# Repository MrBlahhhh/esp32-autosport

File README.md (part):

# ESP32-S3 CAN + microSD Automotive Logger — Rev B

## TL;DR

A data logger you wire straight into a race car: 12 V and CAN come in on one
4-pin plug, sensor readings and CAN traffic get written to a microSD card.

- **You cannot kill it with the wiring.** Battery backwards? Blocks it,
  forever, no blown fuse. Alternator load dump, jump start, ignition spikes?
  Clamped. A sensor wire shorted to 12 V? That channel's fuse trips, the
  board keeps logging.
- **Ignition-off doesn't corrupt the card.** The board sees the power cut
  ~150 ms before it actually dies and uses that time (banked in two big
  capacitors) to finish the write and close the file.
- **4 sensor inputs, jumper-set for 0–3.3 V / 0–5 V / 0–16 V**, readable
  fast-and-rough on the ESP32's own ADC or slow-and-precise on a 16-bit
  ADS1115. Plus battery voltage monitoring, USB-C, a WS2812 shift-light
  header, and spare I/O.
- **The Python in `gen/` is the real source.** It generates, places, routes,
  audits, and circuit-simulates the whole board; the KiCad files are build
  outputs. `python gen/build_board.py` rebuilds the PCB from nothing, and
  [`gen/README.md`](gen/README.md) documents the whole pipeline — including
  the schematic-drawing conventions — so the next board can reuse it.
- **The firmware runs before the board exists.** `gen/simulate_firmware.py`
  compiles the sketch for the PC against a model of this board and feeds it
  CAN frames, sensor voltages and an ignition cut. Porting the proven MINI R53
  shift-light firmware to this hardware turned up five defects that no ERC,
  DRC or SPICE run can see — including a wideband that reads 17 % high and a
  sensor rail that never powers up.
- **State: routed clean, simulated, firmware ported, never manufactured.**
  Order a small prototype run first.

---

A single-CAN, single-microSD ESP32-S3 board with a motorsport-grade front end:
reverse-battery protection that survives being hooked up backwards indefinitely,
load-dump clamping, and four analog sensor inputs whose dividers are selected by
solder jumpers.

Feature set is deliberately close to the Autosport Labs ESP32-CAN-X2 and the
ESP32 Dual CAN-FD dev board — same ESP32-S3-WROOM-1 module, same 4-pin JST-PH
harness convention (12 V / GND / CAN_H / CAN_L), same jumper-selectable 120 Ω
termination — but trades the second CAN channel for an onboard microSD socket
and conditioned analog inputs. Termination ships **off** here rather than on,
which is the one place this board deliberately breaks with that convention:
the common case is plugging into a vehicle bus that is already terminated.

**Status: Rev B, fully routed.** Schematic is ERC-clean on KiCad 9.0. The PCB
is **84 x 100 mm**, 4-layer, **fully placed and routed with zero DRC errors and
nothing unconnected** — 1731 tracks, 323 vias, 206 footprints, 115 nets. Rev B
carries the fixes from an external datasheet review (§7): the LM74700 enable
divider, the ANODE capacitor, two TVS standoff corrections, transient clamps
on the analog harness inputs, and a dozen smaller items. `fab/` holds the
Gerbers, drill, BOM and pick-and-place in JLCPCB's format, BOM and CPL verified
to list the same 167 designators. See §9 for how the board is built, §10 for
what simulation and the physical audit say about it, and §11 for
the ordering steps. **Nothing has ever been fabricated — the first order should
be a small prototype run.**

---

## 1. Specification

| | |
|---|---|
| MCU | ESP32-S3-WROOM-1-N16R8 (16 MB flash, 8 MB octal PSRAM) |
| Supply input | 6–36 V continuous, reverse-protected to −65 V, transients clamped at 64.5 V, 154 ms power-cut ride-through (51 ms worst-case on a flat battery) |
| CAN | 1× CAN 2.0B, TJA1051T/3, ESP32-S3 TWAI controller, split termination, **off by default** |
| Storage | microSD, 4-bit SDMMC, switchable card supply |
| Analog in | 4 channels, solder-jumper divider, **0–5 V by default** (0–3.3 V / 0–16 V by jumper) + optional pull-up bias, shared by the ESP32 ADC and a 16-bit ADS1115 |
| Extras | Battery voltage monitor, USB-C (native USB), I²C/Qwiic, UART0, SPI breakout, WS2812 5 V DIN header, 6-pin spare-IO header |
| Rails | +5 V @ 1 A, +3V3 @ 1 A, +5 V sensor excitation (separately fused) |
| Parts | 195 component instances, 97 distinct BOM lines, all surface-mount except 8 through-hole connectors |

---

## 2. Power chain

```
J1.1 ──[F1 2A]──┬──[FB1 ferrite]── LM74700-Q1 + Q1 (ideal diode) ──┬── +VBAT
                │                                                  ├── C3 100µF bulk
                └── D1 SMCJ40CA clamp                              ├── U3 LM5164 ─→ +5V ─[PF1]─→ +5VS
                    (ahead of the FET)                             └── U4 LM5164 ─→ +3V3
```

### Reverse-battery protection

`U1` (LM74700-Q1) drives `Q1`, a 100 V N-channel MOSFET, as an ideal diode.
`Q1`'s **source faces the battery and its drain faces the load**, so the body
diode points forward: current passes in normal operation, and with the battery
connected backwards the body diode is reverse-biased and the FET is held off.
Nothing conducts, nothing gets hot, and the fuse does not blow — you can hook it
up backwards all day.

The forward drop is the FET's I·R (6.8 mΩ × 0.5 A ≈ 3 mV) rather than a diode's
0.4 V, so nothing is wasted in normal running either.

**Order matters here.** `D1`, the transient clamp, sits *ahead* of the blocking
FET. Clamping downstream of it leaves `Q1` and the LM74700 exposed to whatever
arrives on the harness: on a negative transient `Q1` turns off and stands the
whole pulse across its drain-source, and pulses 1 (−100 V) and 3a (−150 V) both
exceed its 100 V rating. In front of the FET the clamp catches those first —
simulation puts `Q1` at 55 V during pulse 1, against 100 V (§10).

That placement is only safe because `D1` is **bidirectional**. A unidirectional
part in this position would forward-conduct on a sustained reverse connection
and blow `F1`, which is exactly the outcome the ideal diode exists to avoid. At
40 V standoff either way, a −14 V reverse battery is still `Q1`'s job to block
and only real transients are clamped.

`R1`/`R2` set the LM74700 UVLO so the board enables at roughly 5.9 V and drops
out cleanly during cranking rather than browning out in an undefined state.

### Transient rating and its assumption

`D1` is an SMCJ40CA: 40 V standoff either polarity, 64.5 V clamping at 1500 W
(10/1000 µs). 40 V rather than 33 V so the part stands off the declared 36 V
top of the input window instead of sitting in conduction there.

That covers **ISO 7637-2 pulse 5b with centralised load-dump suppression**
(test level ~35 V), which is what any alternator with an internal avalanche
clamp produces — i.e. everything built in the last several decades. Simulation
(§10) shows the harness reaching 31 V in that case with the TVS never
conducting at all. Pulses 1, 2a, 3a and 3b are likewise covered: the worst is
pulse 1, where the clamp takes 0.07 J against roughly 2 J of capability at that
pulse width. A 24 V jump-start sits below the standoff voltage so it does not
conduct.

It does **not** cover unsuppressed load dump. At the pulse 5b level IV of 87 V
the clamp is asked to absorb 219 J against about 6.7 J of capability and is
destroyed (§10). That needs a higher-energy clamp or a series pre-regulator —
**say so if the target vehicle has an external-regulator alternator.**

Both bucks are LM5164s rated to **100 V**, so at the 64.5 V clamp level there
is still headroom on the switcher inputs; the clamp fires before anything
downstream is stressed. The tighter limit is the LM74700's own 65 V, which the
clamp level sits directly on top of — another reason the unsuppressed case is
out of scope rather than marginal.

### Why two bucks instead of a buck plus an LDO

`U3` (+5 V) and `U4` (+3V3) both run directly off `+VBAT`. It costs one extra
inductor versus 12 V→5 V→3.3 V cascading, and buys two things:

1. **Fault isolation.** A shorted 5 V sensor wire in the harness loads `U3`
   and trips `PF1`, but `U4` and the MCU never see it. A cascaded 3.3 V rail
   would collapse with the 5 V rail.
2. **No heat.** A 5 V→3.3 V linear at 600 mA burns ~1 W, which in an engine
   bay at 85 °C ambient is a thermal problem in a small package. A switcher
   burns almost nothing.

Both parts are the same LM5164, so it is one line on the BOM in quantity 20
rather than two different regulators.

### Power-fail detection and ride-through

The ignition cuts this board's power with a log file open on the SD card,
every single drive. The chain that makes that survivable:

1. **Detect** — a TLV431 watches `VBAT_F` *ahead* of Q1 through a 100k/12.7k
   divider and asserts `PWR_FAIL` (GPIO15, rising edge) when the harness
   drops below **11.0 V**. Sensing ahead of the ideal diode is the point:
   when the ignition opens, the harness collapses within microseconds while
   `+VBAT` coasts, so the warning arrives before any stored energy has been
   spent. A 1 M feedback resistor adds ~0.3 V of hysteresis so cranking sag
   cannot chatter the interrupt.
2. **Coast** — `+VBAT` holds 760 µF (100 µF + 2 × 330 µF/100 V). Energy is
   ½CV², so the bank lives on the input rail where a volt is worth most.
3. **Shed** — `SENS_EN` (GPIO16) drives a 2N7002 + AO3401 high-side switch on
   the sensor rail. Sensors are external loads firmware cannot otherwise
   turn off, and at four × 20 mA they double the drain. The switch is off at
   reset — the rail comes up only when firmware asks.

Simulated end to end (§10, `sim/ridethru.png`): detection in under 1 ms, and
from `PWR_FAIL` to the converters dropping out is **154 ms with the sensor
rail shed, 75 ms without** — both measured on the 760 µF bank.

That is the *healthy-battery* case: the ignition opens at 13.5 V and `+VBAT`
starts its coast from there, because `Q1` isolates it from the harness. Open
the ignition on a battery already down at the trip point and the bank starts
at 10.7 V instead — energy goes as V², so that alone is 1.9× less charge. The
Monte Carlo puts that flat-battery corner at **78 ms median, 51 ms at 0.1 %**
with worst-case tolerances (§10). Both are real; they bound opposite ends of
the same event, and firmware should be sized against the 51 ms.

**Firmware contract:** on `PWR_FAIL` rising — drop `SENS_EN`, stop sampling,
flush and close the file, then idle. Do not start a new write while
`PWR_FAIL` is high. The window is guaranteed by hardware; spending it is
firmware's job.

The firmware that spends it now exists and has been run against that window
(§10, *Firmware in the loop*). Measured: the file is closed **31 ms** after
`PWR_FAIL`, leaving 121 ms of the bank unspent, and the card may take up to a
**~130 ms** flush before the close no longer fits — though that, too, is
against the nominal window; on the flat-battery corner the budget is 51 ms and
only a healthy card fits. That is roughly seven times a
healthy card's latency but it is a limit, not unlimited protection — a card
that stalls for longer than that still loses the file.

### Reversed 5 V on the exposed 5 V pins

Asked and answered per connector: **USB-C** cannot be reversed through the
connector (VBUS/GND positions are fixed; the plug is rotation-symmetric).
**J10 sensor +5VS** survives a reversed 5 V by design — D3 forward-conducts
at −0.7 V and PF1 trips, resettable. A **backwards WS2812 strip** trips PF3;
the strip is on its own. **J8 rail break-out is unprotected** — it is a bare
bench header, and a reversed supply clipped onto it lands directly on the
+5 V rail's loads. Treat J8 like any bare rail.

### 5 V sensor excitation

`+5VS` is the +5 V rail behind the `SENS_EN` load switch, `PF1` (200 mA hold
/ 400 mA trip polyfuse), a ferrite, and `D3` (SMAJ6.0A). A sensor wire
shorted to chassis or to battery trips the polyfuse and clamps the transient
without taking the board down — and a tripped rail can now also be cycled
from firmware instead of waiting for the polyfuse to cool.

Note this is a *fused tap off the 5 V rail*, not a separately regulated
reference. For ratiometric sensors where absolute accuracy matters, the ADC
should ratio against a measurement of `+5VS` — or add a dedicated precision
reference. See §7.

---

## 3. Analog input conditioning

Each of the four channels is identical:

```
AINn_IN ──[1k series]──┬─────────[10k]────┬── AINn ──→ ADC
                       │                  │
                  [JPn PULLUP]        [JPn BYPASS] (shorts the 10k)
                       │                  │
                    2.49k             [JPn RANGE] ─┬─[15k]─ GND   (position A)
                       │                           └─[2.21k]─ GND (position B)
                    +5VS                  │
                                    [100nF] + BAT54S clamp to GND / +3V3
```

### Jumper matrix

| RANGE | BYPASS | Input range | Ratio | At the ADC | Clips at | Typical sensor |
|---|---|---|---|---|---|---|
| **A** | open | **0–5.0 V — ships like this** | 0.5769 | 2.885 V at 5.0 V in | 5.37 V in | MAP, TPS, wideband AFR, most 5 V sensors |
| open | **closed** | 0–3.3 V | 1.0000 | 3.300 V at 3.3 V in | 3.10 V in | 3.3 V-native sensor, ratiometric output |
| **B** | open | 0–16 V | 0.1673 | 2.677 V at 16.0 V in | 18.53 V in | Battery-referenced signals, 12 V switch inputs |

**All four channels ship in the 0–5 V position** — `RANGE` bridged 1–2,
`BYPASS` open — because that is what almost every automotive sensor is, and
because it means the firmware's `DIVIDER_GAIN` matches the board as delivered
rather than assuming a jumper somebody has to remember to fit. Cut the 1–2
bridge to move a channel to either of the other two rows.

The upper leg is the 1 k series resistor plus the 10 k, so 11 k against 15 k
gives 15/26 = 0.5769 on the 5 V range and 2.21/13.21 = 0.1673 on the 16 V one.

**These deliberately do not divide to 3.3 V.** The ESP32-S3 ADC tops out near
3.10 V at 12 dB attenuation, and a divider scaled to land exactly there has no
margin: a 5 V sensor rail is rarely exactly 5.000 V, and anything that
overshoots clips silently at full scale — which reads as a plausible-but-wrong
value rather than an obvious fault. At 0.5769 a 5 V channel does not clip until
5.37 V in. The 1:1 mode is the exception and has no headroom by design; it
assumes a sensor that genuinely cannot exceed 3.3 V. The BAT54S clamps protect
the pin either way, but clamping is protection, not measurement.

Source impedance at the ADC node is 11 k ∥ 15 k = **6.35 kΩ** on the 5 V range
(1.84 kΩ on the 16 V range). With the 100 nF filter cap that puts the −3 dB
point at about 250 Hz — ideal for AFR, temperature and pressure, and the limit
if you ever want something fast on a channel.

`PULLUP` is independent of the above: closing it puts 2.49 kΩ to `+5VS` on the
input node, turning the channel into a bias network for **2-wire NTC sensors**
(coolant, oil, air temp) or open-collector/switch-to-ground inputs. Leave it
open for anything that drives its own output.

Every channel lands on **ADC1** (`GPIO1`, `GPIO2`, `GPIO4`, `GPIO5`), which is
the half of the ESP32-S3 ADC that keeps working while WiFi is active. ADC2 is
unusable with WiFi up — that constraint drove the pin assignment.

The same four conditioned nodes also feed `U13`, an **ADS1115** (16-bit
delta-sigma, on the existing I²C bus at 0x48). The ESP32-S3's internal ADC is
only good for ±1–2 % even after calibration — ±0.2 AFR on a 0–5 V wideband
output — so firmware picks per channel: fast-and-rough on the internal ADC, or
slow-and-accurate (up to 860 SPS) on the ADS1115. The divider resistors are
0.1 % thin-film so the front end does not throw away what the converter buys,
and the note in the schematic records that the 1 k series resistor is part of
the divider chain — the exact scale factor is a firmware calibration constant.

`R77` (100 k) and `R64` (10 k) divide `+VBAT` by 11 onto `GPIO6` for
battery-voltage logging: 14.0 V reads 1.27 V, and the 36 V top of the input
range reads 3.27 V.

---

## 4. CAN

`U12` is a TJA1051T/3 — 5 V bus drive with a separate `VIO` pin tied to +3V3, so
the ESP32 sees 3.3 V logic with no level shifter. `S` is pulled low by `R54`
(10 k) so the transceiver comes up in normal mode with the MCU still in reset;
`GPIO21` can raise it for silent (listen-only) sniffing. `CAN_TX` has no
external pull — the TJA1051 pulls TXD high internally, so a floating pin at
boot is recessive and a bare board cannot jam the bus.

Bus side, in order from the transceiver out:

- `L3` common-mode choke — TDK ACT45B-510-2P-TL003, 51 µH, AEC-Q200. The
  footprint is project-local (`footprints/esp32autosport.pretty`) and its pads
  are renumbered so the symbol's winding 1–2 maps to the package.
- Split termination: `R55`/`R56`, two 60.4 Ω in series with `C28` 4.7 nF to
  ground at the midpoint. Split termination beats a single 120 Ω resistor
  because it gives the common-mode noise somewhere to go instead of
  reflecting it.
- `JP1` in series with the top half — **open by default: the board ships
  unterminated**. Bridge the pads only when this board is an end node on a bus
  of its own. Every vehicle bus, OBD-II diagnostics included, is already
  terminated at both ends, and a third 120 Ω across the pair takes it to about
  40 Ω and can stop it working. This deliberately departs from the Autosport
  Labs convention of shipping terminated, because the common case here is
  plugging into a car that is already correct.
- `D6`/`D7` SMAJ26CA bidirectional clamps to ground on each line.

CAN_H/CAN_L run to `J1` pins 3 and 4, so one 4-pin JST-PH carries power and bus
in a single harness.

### OBD-II and "K-DCAN"

A BMW/MINI K+DCAN cable carries **two unrelated buses**, and this board has
hardware for exactly one of them.

**D-CAN — yes, already.** Diagnostic CAN is ISO 15765-4: plain 500 kbit/s CAN
on OBD-II pins 6 and 14, which is what `U12` and the TWAI controller do. `J1`
maps onto an OBD-II plug with nothing in between — pin 16 to `J1.1`, pins 4/5
to `J1.2`, pin 6 to `J1.3`, pin 14 to `J1.4` — so one cable both powers the
board and connects it to the bus. What is left is software: ISO-TP
(ISO 15765-2) segmentation and whichever of UDS or KWP2000 the target speaks.

> **Termination is already off.** `JP1` ships open (§4), which is what a
> vehicle bus wants — it is already terminated at both ends, and a third
> 120 Ω across the pair drops it to ~40 Ω and can stop it working entirely.
> So there is nothing to cut before plugging into a car; bridge `JP1` only
> for a bench bus where this board is an end node. Note also
> that `CAN_S` (GPIO21) lets firmware pick listen-only for sniffing, so the
> board need never ACK a bus it is only observing.

**K-line — no, and it cannot be bodged.** ISO 9141-2 / KWP2000 is a single
bidirectional wire on OBD-II pin 7 idling at battery voltage and pulled to
ground by an open-collector driver. That needs a transceiver — an L9637D or
equivalent — and there is none on this board. Feeding it into an analog input
does not work either: on the 0–16 V setting the anti-alias filter rolls off at
891 Hz (§10), which destroys even 9600 baud, and it gives no way to transmit.
Routing it to `J7` is worse, since those are strapping pins and a K-line
idling high at boot would hold `IO46` in the wrong boot mode.

This matters for the **MINI R53** specifically: its instrument CAN carries
`0x316` at 500 kbit/s, which this board already reads and logs — but its
*diagnostics and flashing* are K-line at 9600 8E1, negotiating to 62500 baud
for flash reads. The shift light and telemetry work on this hardware. A
tuning or flashing tool does not.

Adding it needs an external L9637D module on the `J5` SPI header — the S3's
UARTs matrix onto any GPIO, so two of `GPIO40`–`42`/`47` become K-line TX/RX,
and `J5` supplies +3V3 and ground. The one wire `J5` cannot supply is the
transceiver's battery feed: `J8` breaks out +5 V, +3V3 and ground only, so
12 V has to come from `TP3` or upstream of `J1`. **For a rev C, an on-board
L9637D is the highest-value addition** — SO-8, about a dollar, two GPIOs and a
`+VBAT` tap — and it would make one board cover both halves of a K+DCAN cable.

---

## 5. microSD

Wired for **4-bit SDMMC** (`GPIO9`–`GPIO14`), not SPI — roughly 4× the write
throughput, which matters when logging a busy bus.

- 33 Ω series damping on CLK, CMD and D0–D3.
- 10 kΩ pull-ups on CMD and D0–D3, the value Espressif's SD documentation
  asks for. **These pull to `SD_VDD`, the switched rail, not to +3V3** —
  pull-ups to a permanent rail would back-feed a powered-down card through
  its ESD structures. The pull-up on D3 is also what selects SD mode over
  SPI mode when the card powers up. Card detect keeps a weaker 47 kΩ: it is
  a mechanical contact, not a bus line, so there is no reason to burn the
  standing current.
- `Q6`/`Q7` form a high-side switch on the card supply, driven by `GPIO7`, so
  firmware can hard power-cycle a card that has locked up mid-write. This is
  the single most useful recovery mechanism in a logger; SD cards do wedge.
- `GPIO8` reads the socket's card-detect switch.

**Firmware note:** tristate the SDMMC pins before dropping `SD_PWR_EN`, or the
MCU will back-feed the card through its I/O pins while its supply is off.

---

## 6. GPIO map

| Module pin | GPIO | Net | Function |
|---|---|---|---|
| 39 | IO1 | `AIN1` | Analog ch 1 (ADC1_CH0) |
| 38 | IO2 | `AIN2` | Analog ch 2 (ADC1_CH1) |
| 4 | IO4 | `AIN3` | Analog ch 3 (ADC1_CH3) |
| 5 | IO5 | `AIN4` | Analog ch 4 (ADC1_CH4) |
| 6 | IO6 | `VBAT_SNS` | Battery voltage ÷11 (ADC1_CH5) |
| 7 | IO7 | `SD_PWR_EN` | microSD supply enable (high = on) |
| 12 | IO8 | `SD_CD` | Card detect |
| 17–22 | IO9–IO14 | `SD_D3,D2,D1,D0,CMD,CLK` | SDMMC 4-bit |
| 10, 11 | IO17, IO18 | `CAN_TX`, `CAN_RX` | TWAI |
| 23 | IO21 | `CAN_S` | Transceiver silent mode (low = normal) |
| 13, 14 | IO19, IO20 | `USB_DM`, `USB_DP` | Native USB |
| 31, 32 | IO38, IO39 | `I2C_SDA`, `I2C_SCL` | Qwiic header |
| 36, 37 | IO44, IO43 | `UART_RX`, `UART_TX` | UART0 header |
| 33–35, 24 | IO40–42, IO47 | `SPI_SCK`, `SPI_MISO`, `SPI_MOSI`, `SPI_CS` | SPI breakout |
| 25 | IO48 | `LED_DIN_MCU` | WS2812 data (via 5 V AHCT buffer → header) |
| 27 | IO0 | `MCU_BOOT` | BOOT button |
| 3 | EN | `MCU_EN` | RESET button |
| 15, 16, 26 | IO3, IO46, IO45 | — | Spare-IO header `J7`, each with a 10 k pull-down |
| 8 | IO15 | `PWR_FAIL` | Power-fail interrupt (high = harness below 11 V); also J7 pin 4 as a probe point |
| 9 | IO16 | `SENS_EN` | Sensor-rail (+5VS) enable, active high, off at reset; also J7 pin 5 |
| 28, 29, 30 | IO35, IO36, IO37 | — | **Unusable** — octal PSRAM |

`IO3`, `IO45` and `IO46` are strapping pins, and each carries a 10 kΩ
pull-down (`R36`–`R38`) chosen for its strapping role: `IO45` low sets
VDD_SPI to 3.3 V, `IO46` low selects normal boot, `IO3` low fixes the JTAG
source. The board therefore boots correctly with `J7` empty. What the
pull-downs cannot survive is something plugged into `J7` that actively
*drives* one of them high at boot — 10 kΩ loses to a driver — so do not hang
anything on `J7` that asserts a level before the MCU is out of reset.

### WS2812 shift-light header

`J6` (silk **WS2812**): `LED_5V` / `LED_DIN` / `GND`. `LED_DIN` is driven by a
`74AHCT1G125` powered from `+5V`, so the strip sees a real 5 V logic level.
Firmware bit-bangs / RMT on **GPIO48**. `LED_5V` is behind a 0.5 A polyfuse off
the board 5 V rail — enough for an 8-LED stick, not a full belly-band.

### SPI breakout

`+3V3` / `GND` / `SCK` / `MISO` / `MOSI` / `CS` on GPIO40/41/42/47. Intended for
an external MCP2515 (second CAN), CC1101 (433 MHz TPMS), or MAX6675, etc.

---

## 7. Review before layout

Resolved in the rev A review (2026-08, against datasheet SNVSAU4D and TI
drawing 4214849/B):

1. ~~RON placeholders~~ — computed from Eq. 12: **31.6 kΩ → 396 kHz** on the
   5 V rail, **20.5 kΩ → 402 kHz** on the 3.3 V rail. Minimum on-time at the
   64.5 V clamp is 196 ns / 128 ns, both far above the 50 ns floor.
2. ~~Footprint~~ — the original `EP2.41x3.3mm` exposed pad was *smaller* than
   the DDA0008B pad itself (max 2.71 × 3.4 mm). Now on
   `EP2.95x4.9mm_Mask2.71x3.4mm_ThermalVias`, which matches TI's example land
   pattern exactly (2.95 × 4.9 copper, 2.71 × 3.4 mask-defined opening).
3. ~~Load-dump assumption~~ — confirmed: the target vehicle's alternator never
   exceeds 20 V, so the SMCJ40CA's 40 V standoff has comfortable margin and the
   centralised-suppression assumption in §2 holds. Simulation later put a
   number on what happens if it does not: see §10.
4. ~~Clamp injection~~ — quantified: one analog input shorted to 20 V battery
   back-feeds ≈1.6 mA through its BAT54S into +3V3. With the MCU running
   (≥ 20 mA) the rail cannot lift, but in deep sleep the always-on load is only
   ≈1.3 mA (power LED), so one faulted channel floats the rail to ≈3.6 V and
   two would exceed the ESP32's absolute maximum. Fixed with `D2`, a 3.6 V
   zener rail clamp (MM3Z3V6T1G).

Two more issues surfaced while reading the datasheet, both fixed:

- **Bootstrap capacitors were 100 nF.** The LM5164 datasheet mandates exactly
  2.2 nF and warns that larger values overstress the internal VCC regulator
  and damage the device. Both `CBST` are now 2.2 nF 50 V X7R.
- **No feedback ripple injection.** The outputs are all-ceramic, so FB had no
  in-phase ripple — the datasheet (Table 6-1) says a COT converter is unstable
  without it. Both rails now carry a Type-3 network (RA from SW, CA to the
  output, CB into FB: 121 k / 3.3 nF / 270 pF on 5 V, 95.3 k / 3.3 nF / 270 pF
  on 3.3 V), sized per TI's design example for ≈20 mV of ramp at 14 V in.

5. ~~ESP32-S3 ADC linearity~~ — resolved for the AFR use case: `U13`, an
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
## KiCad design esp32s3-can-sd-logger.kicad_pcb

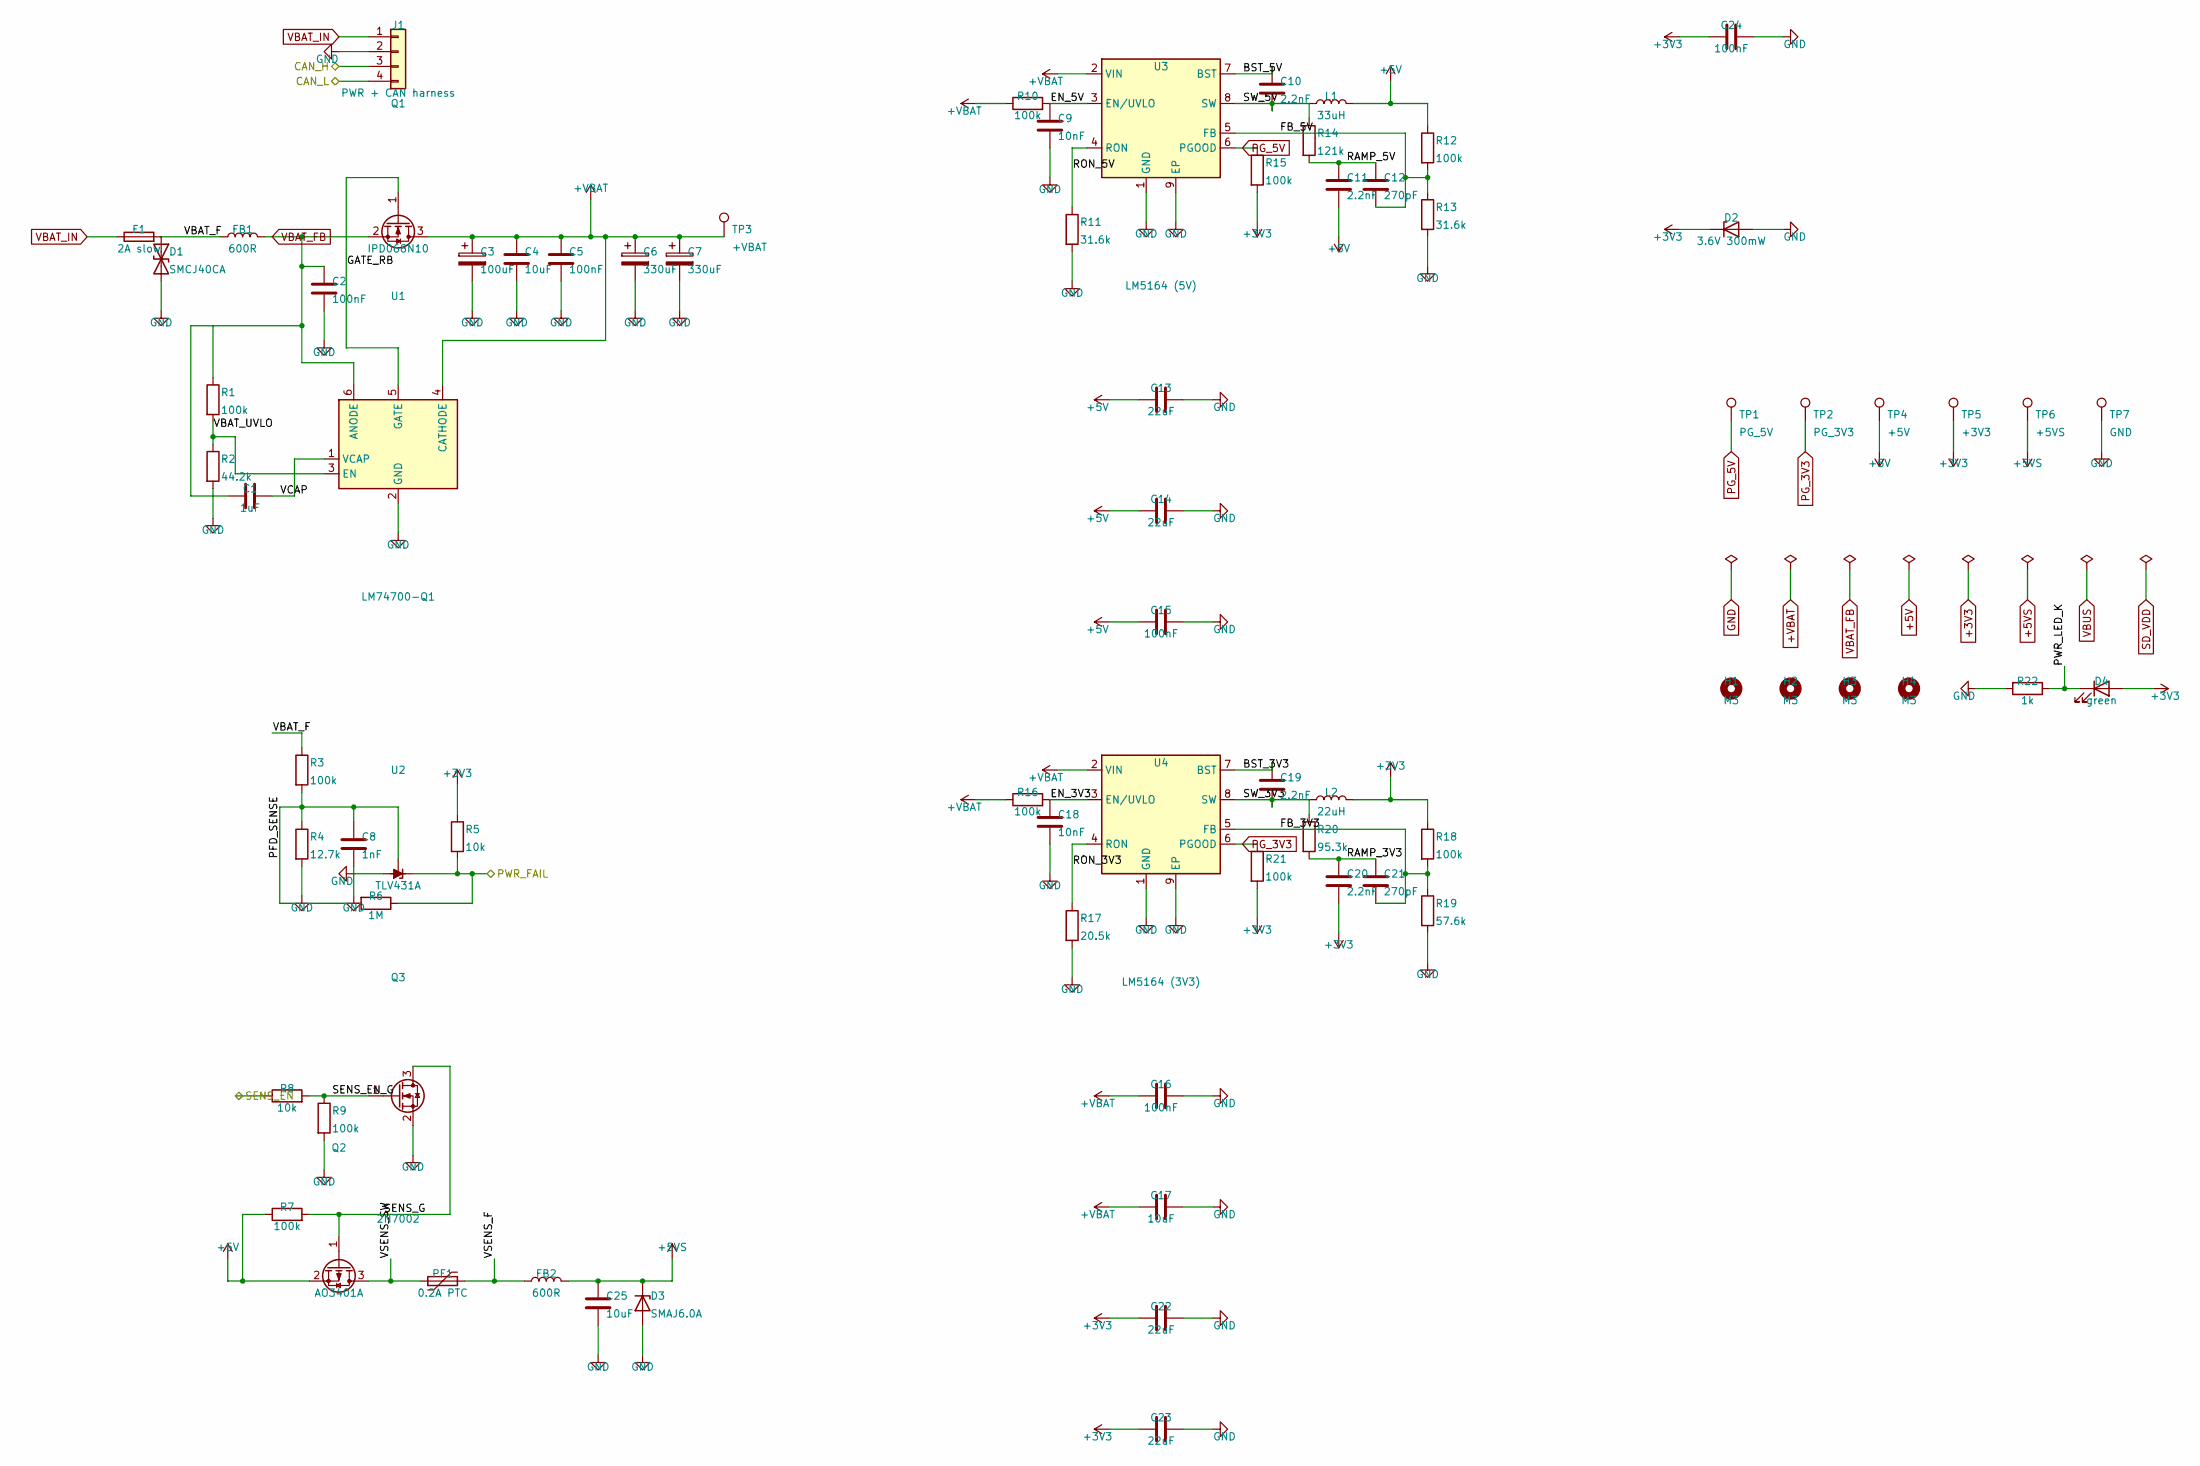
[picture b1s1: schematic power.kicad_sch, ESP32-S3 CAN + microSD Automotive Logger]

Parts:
C1: 1uF; C_0805_2012Metric; Voltage 50V
C2, C5, C16: 100nF; C_0805_2012Metric; Voltage 100V
C3: 100uF; CP_Elec_10x10.5; Voltage 100V; MPN Nichicon UCD2A101MNL1GS
C4, C17: 10uF; C_1206_3216Metric; Voltage 100V
C6, C7: 330uF; CP_Elec_16x22; Voltage 100V
C8: 1nF; C_0805_2012Metric; Voltage 50V
C9, C18: 10nF; C_0805_2012Metric; Voltage 100V
C10, C11, C19, C20: 2.2nF; C_0805_2012Metric; Voltage 50V
C12, C21: 270pF; C_0805_2012Metric; Voltage 50V
C13, C14, C22, C23: 22uF; C_1206_3216Metric; Voltage 16V
C15, C24: 100nF; C_0805_2012Metric; Voltage 16V
C25: 10uF; C_1206_3216Metric; Voltage 16V
D1: SMCJ40CA; D_SMC; MPN Littelfuse SMCJ40CA
D2: 3.6V 300mW; D_SOD-323; MPN onsemi MM3Z3V6T1G
D3: SMAJ6.0A; D_SMA; MPN Littelfuse SMAJ6.0A
D4: green; LED_0805_2012Metric
F1: 2A slow; Fuse_1206_3216Metric; MPN Littelfuse 0466002.NR
FB1: 600R; L_1206_3216Metric; MPN Wurth 742792625
FB2: 600R; L_0805_2012Metric; MPN Wurth 742792022
H1, H2, H3, H4: M3; MountingHole_3.2mm_M3
J1: PWR + CAN harness; JST_PH_B4B-PH-K_1x04_P2.00mm_Vertical; MPN JST B4B-PH-K-S(LF)(SN)
L1: 33uH; L_Sunlord_SWPA8040S; MPN Sunlord ASWPA8050S330MT
L2: 22uH; L_Sunlord_SWPA8040S; MPN Sunlord ASWPA8050S220MT
PF1: 0.2A PTC; R_1206_3216Metric; MPN Bourns MF-MSMF020
Q1: IPD068N10; TO-252-3_TabPin2; MPN Infineon IPD068N10N3G
Q2: AO3401A; SOT-23; MPN Alpha & Omega AO3401A
Q3: 2N7002; SOT-23; MPN onsemi 2N7002
R1, R7, R9, R10, R12, R15, R16, R18, R21: 100k; R_0805_2012Metric
R2: 44.2k; R_0805_2012Metric
R3: 100k; R_0805_2012Metric; Tolerance 1%
R4: 12.7k; R_0805_2012Metric; Tolerance 1%
R5, R8: 10k; R_0805_2012Metric
R6: 1M; R_0805_2012Metric
R11, R13: 31.6k; R_0805_2012Metric
R14: 121k; R_0805_2012Metric
R17: 20.5k; R_0805_2012Metric
R19: 57.6k; R_0805_2012Metric
R20: 95.3k; R_0805_2012Metric
R22: 1k; R_0805_2012Metric
TP1: PG_5V; TestPoint_Pad_D1.5mm
TP2: PG_3V3; TestPoint_Pad_D1.5mm
TP3: +VBAT; TestPoint_Pad_D1.5mm
TP4: +5V; TestPoint_Pad_D1.5mm
TP5: +3V3; TestPoint_Pad_D1.5mm
TP6: +5VS; TestPoint_Pad_D1.5mm
TP7: GND; TestPoint_Pad_D1.5mm
U1: LM74700-Q1; SOT-23-6; MPN LM74700QDBVRQ1
U2: TLV431A; SOT-23; MPN TLV431ASN1T1G
U3: LM5164 (5V); SOIC-8-1EP_3.9x4.9mm_P1.27mm_EP2.95x4.9mm_Mask2.71x3.4mm_Th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; MPN LM5164DDAR
U4: LM5164 (3V3); SOIC-8-1EP_3.9x4.9mm_P1.27mm_EP2.95x4.9mm_Mask2.71x3.4mm_Th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; MPN LM5164DDAR

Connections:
+3V3: C20.2, C22.1, C23.1, C24.1, D2.1 (K), D4.2 (A), L2.2, R5.1, R15.2, R18.1, R21.2, TP5.1; also elsewhere on the board
+5V: C11.2, C13.1, C14.1, C15.1, L1.2, Q2.2 (S), R7.1, R12.1, TP4.1; also elsewhere on the board
+5VS: C25.1, D3.1 (K), FB2.2, TP6.1; also elsewhere on the board
+VBAT: C3.1, C4.1, C5.1, C6.1, C7.1, C16.1, C17.1, Q1.3 (D), R10.1, R16.1, TP3.1, U1.4 (CATHODE), U3.2 (VIN), U4.2 (VIN); also elsewhere on the board
BST_3V3: C19.1, U4.7 (BST)
BST_5V: C10.1, U3.7 (BST)
CAN_H: J1.3; also elsewhere on the board
CAN_L: J1.4; also elsewhere on the board
EN_3V3: C18.1, R16.2, U4.3 (EN/UVLO)
EN_5V: C9.1, R10.2, U3.3 (EN/UVLO)
FB_3V3: C21.2, R18.2, R19.1, U4.5 (FB)
FB_5V: C12.2, R12.2, R13.1, U3.5 (FB)
GATE_RB: Q1.1 (G), U1.5 (GATE)
PFD_SENSE: C8.1, R3.2, R4.1, R6.2, U2.2 (REF)
PG_3V3: R21.1, TP2.1, U4.6 (PGOOD)
PG_5V: R15.1, TP1.1, U3.6 (PGOOD)
PWR_FAIL: R5.2, R6.1, U2.1 (K); also elsewhere on the board
PWR_LED_K: D4.1 (K), R22.1
RAMP_3V3: C20.1, C21.1, R20.2
RAMP_5V: C11.1, C12.1, R14.2
RON_3V3: R17.1, U4.4 (RON)
RON_5V: R11.1, U3.4 (RON)
SENS_EN: R8.1; also elsewhere on the board
SENS_EN_G: Q3.1 (G), R8.2, R9.1
SENS_G: Q2.1 (G), Q3.3 (D), R7.2
SW_3V3: C19.2, L2.1, R20.1, U4.8 (SW)
SW_5V: C10.2, L1.1, R14.1, U3.8 (SW)
VBAT_F: D1.1 (A1), F1.2, FB1.1, R3.1
VBAT_FB: C1.2, C2.1, FB1.2, Q1.2 (S), R1.1, U1.6 (ANODE)
VBAT_IN: F1.1, J1.1
VBAT_UVLO: R1.2, R2.1, U1.3 (EN)
VCAP: C1.1, U1.1 (VCAP)
VSENS_F: FB2.1, PF1.2
VSENS_SW: PF1.1, Q2.3 (D)

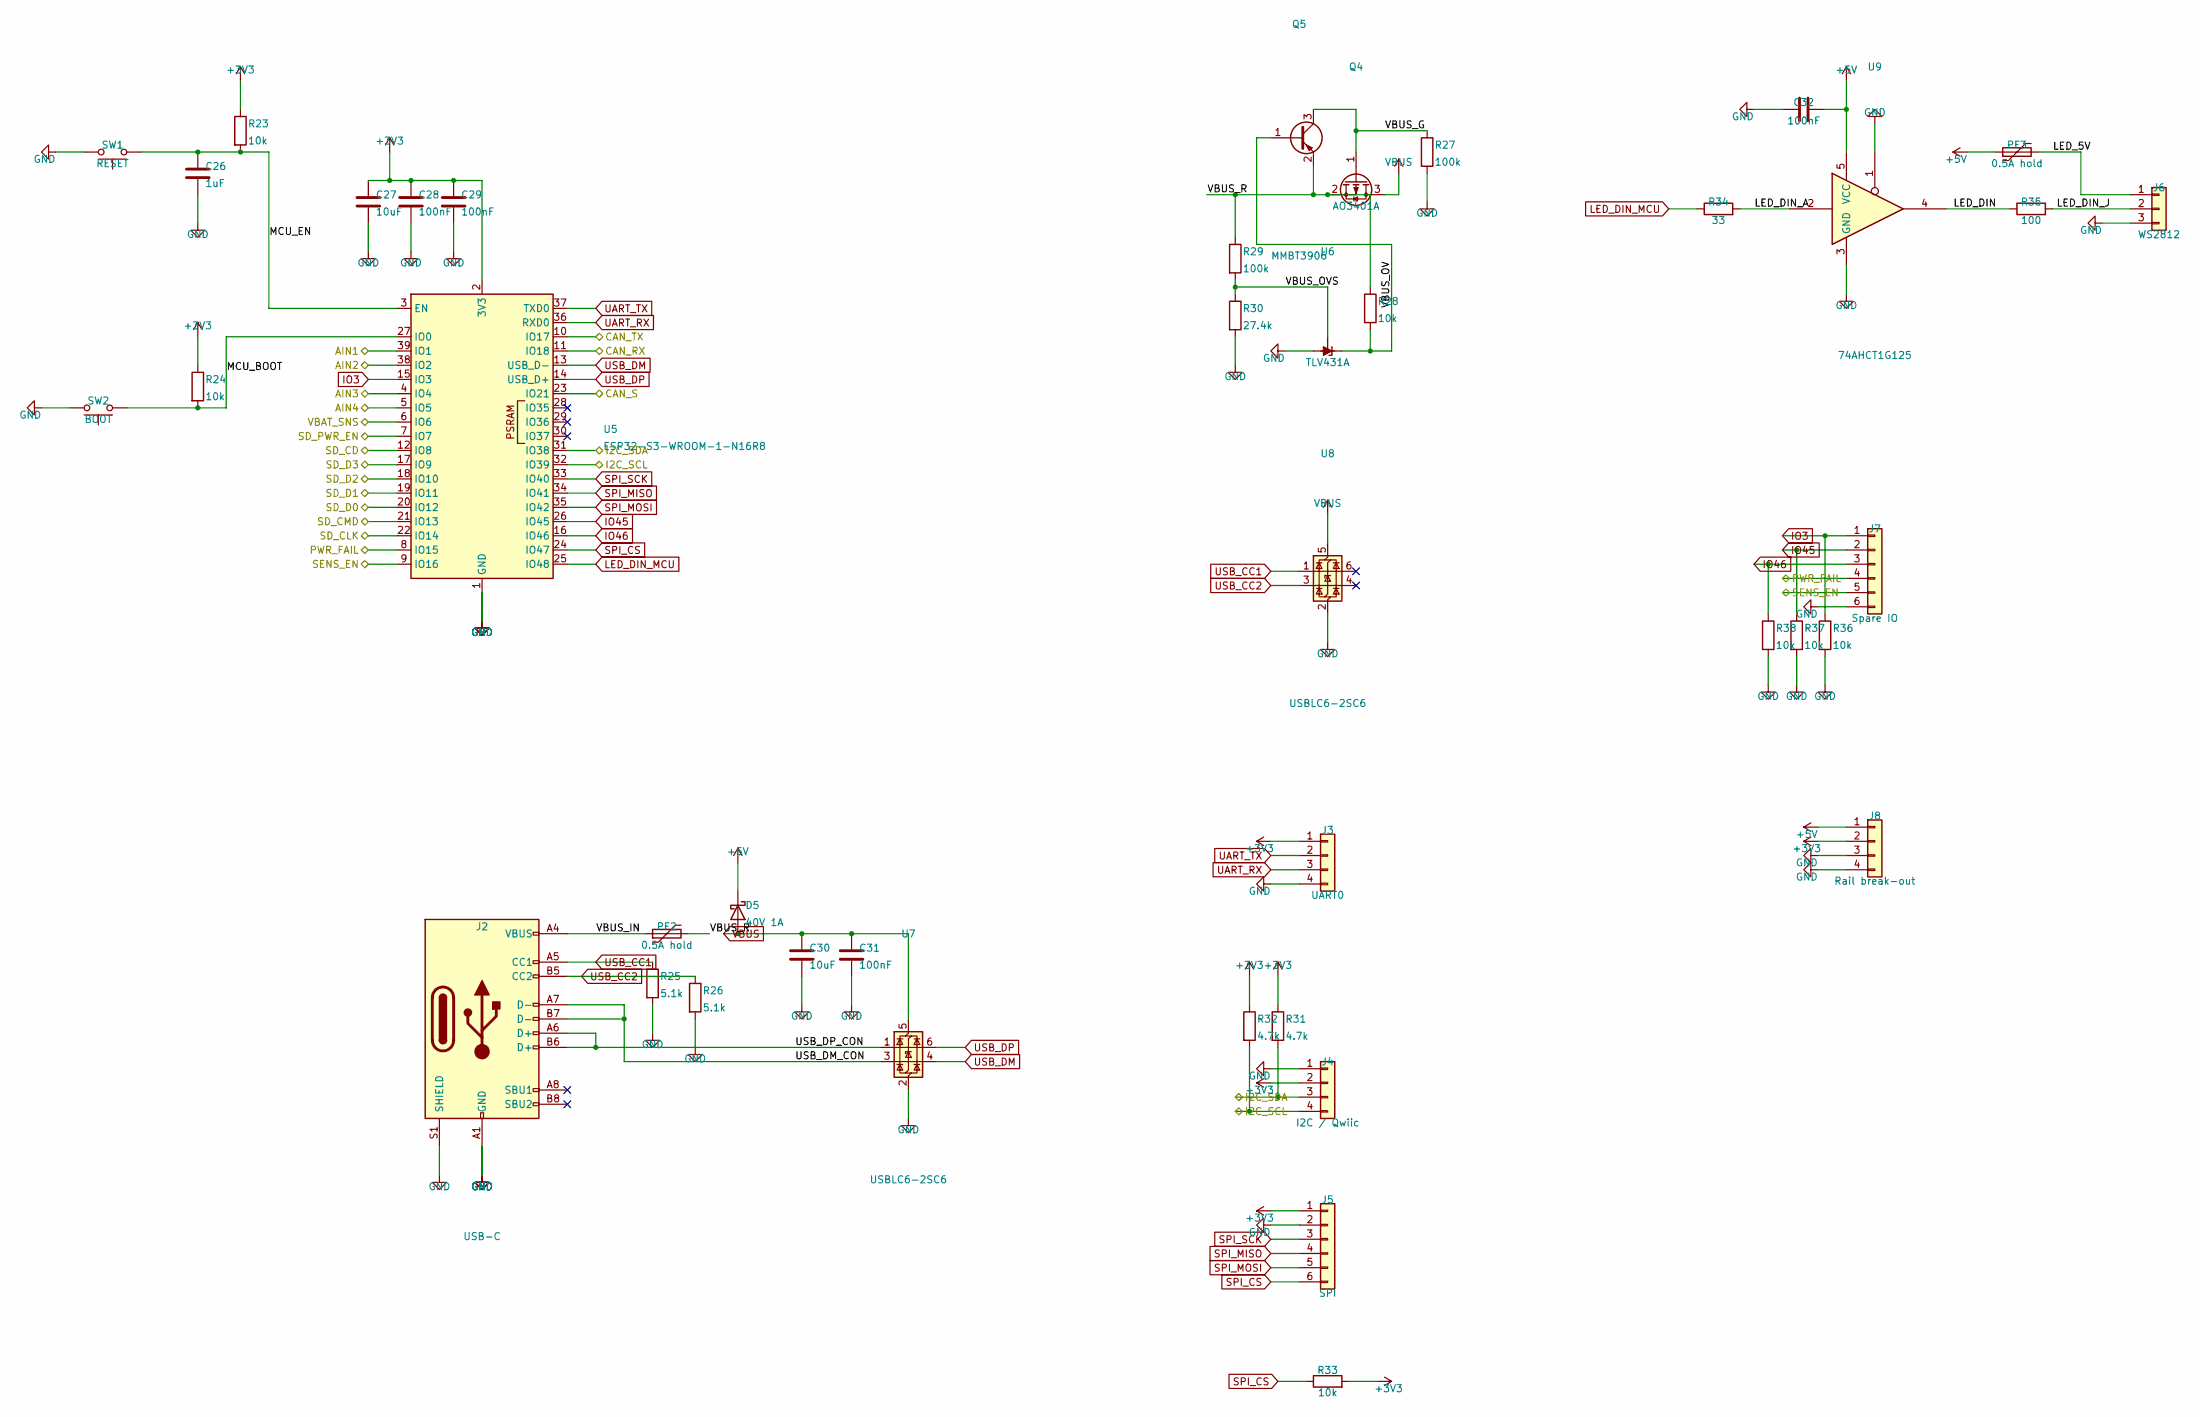
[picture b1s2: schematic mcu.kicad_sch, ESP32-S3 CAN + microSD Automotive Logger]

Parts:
C26: 1uF; C_0805_2012Metric; Voltage 16V
C27, C30: 10uF; C_1206_3216Metric; Voltage 16V
C28, C29, C31, C32: 100nF; C_0805_2012Metric; Voltage 16V
D5: 40V 1A; D_SOD-123; MPN PMEG4010
J2: USB-C; USB_C_Receptacle_HRO_TYPE-C-31-M-12; MPN HRO TYPE-C-31-M-12
J3: UART0; PinHeader_1x04_P2.54mm_Vertical
J4: I2C / Qwiic; PinHeader_1x04_P2.54mm_Vertical
J5: SPI; PinHeader_1x06_P2.54mm_Vertical
J6: WS2812; PinHeader_1x03_P2.54mm_Vertical
J7: Spare IO; PinHeader_1x06_P2.54mm_Vertical
J8: Rail break-out; PinHeader_1x04_P2.54mm_Vertical
PF2, PF3: 0.5A hold; R_1206_3216Metric; MPN Bourns MF-MSMF050
Q4: AO3401A; SOT-23; MPN Alpha & Omega AO3401A
Q5: MMBT3906; SOT-23; MPN onsemi MMBT3906
R23, R24, R28, R33, R36, R37, R38: 10k; R_0805_2012Metric
R25, R26: 5.1k; R_0805_2012Metric
R27: 100k; R_0805_2012Metric
R29: 100k; R_0805_2012Metric; Tolerance 1%
R30: 27.4k; R_0805_2012Metric; Tolerance 1%
R31, R32: 4.7k; R_0805_2012Metric
R34: 33; R_0805_2012Metric
R35: 100; R_0805_2012Metric
SW1: RESET; SW_SPST_TL3342; MPN TL3342F160QG
SW2: BOOT; SW_SPST_TL3342; MPN TL3342F160QG
U5: ESP32-S3-WROOM-1-N16R8; ESP32-S3-WROOM-1; MPN ESP32-S3-WROOM-1-N16R8
U6: TLV431A; SOT-23; MPN TLV431ASN1T1G
U7, U8: USBLC6-2SC6; SOT-23-6; MPN USBLC6-2SC6
U9: 74AHCT1G125; SOT-23-5; MPN SN74AHCT1G125DBVR

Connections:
+3V3: C27.1, C28.1, C29.1, J3.1, J4.2, J5.1, J8.2, R23.1, R24.1, R31.1, R32.1, R33.2, U5.2 (3V3); also elsewhere on the board
+5V: C32.1, D5.1 (K), J8.1, PF3.1, U9.5 (VCC); also elsewhere on the board
AIN1: U5.39 (IO1); also elsewhere on the board
AIN2: U5.38 (IO2); also elsewhere on the board
AIN3: U5.4 (IO4); also elsewhere on the board
AIN4: U5.5 (IO5); also elsewhere on the board
CAN_RX: U5.11 (IO18); also elsewhere on the board
CAN_S: U5.23 (IO21); also elsewhere on the board
CAN_TX: U5.10 (IO17); also elsewhere on the board
I2C_SCL: J4.4, R32.2, U5.32 (IO39); also elsewhere on the board
I2C_SDA: J4.3, R31.2, U5.31 (IO38); also elsewhere on the board
IO3: J7.1, R36.1, U5.15 (IO3)
IO45: J7.2, R37.1, U5.26 (IO45)
IO46: J7.3, R38.1, U5.16 (IO46)
LED_5V: J6.1, PF3.2
LED_DIN: R35.1, U9.4
LED_DIN_A: R34.2, U9.2
LED_DIN_J: J6.2, R35.2
LED_DIN_MCU: R34.1, U5.25 (IO48)
MCU_BOOT: R24.2, SW2.1, U5.27 (IO0)
MCU_EN: C26.1, R23.2, SW1.1, U5.3 (EN)
PWR_FAIL: J7.4, U5.8 (IO15); also elsewhere on the board
SD_CD: U5.12 (IO8); also elsewhere on the board
SD_CLK: U5.22 (IO14); also elsewhere on the board
SD_CMD: U5.21 (IO13); also elsewhere on the board
SD_D0: U5.20 (IO12); also elsewhere on the board
SD_D1: U5.19 (IO11); also elsewhere on the board
SD_D2: U5.18 (IO10); also elsewhere on the board
SD_D3: U5.17 (IO9); also elsewhere on the board
SD_PWR_EN: U5.7 (IO7); also elsewhere on the board
SENS_EN: J7.5, U5.9 (IO16); also elsewhere on the board
SPI_CS: J5.6, R33.1, U5.24 (IO47)
SPI_MISO: J5.4, U5.34 (IO41)
SPI_MOSI: J5.5, U5.35 (IO42)
SPI_SCK: J5.3, U5.33 (IO40)
UART_RX: J3.3, U5.36 (RXD0)
UART_TX: J3.2, U5.37 (TXD0)
USB_CC1: J2.A5 (CC1), R25.1, U8.1 (I/O1)
USB_CC2: J2.B5 (CC2), R26.1, U8.3 (I/O2)
USB_DM: U5.13 (USB_D-), U7.4 (I/O2)
USB_DM_CON: J2.A7 (D-), J2.B7 (D-), U7.3 (I/O2)
USB_DP: U5.14 (USB_D+), U7.6 (I/O1)
VBAT_SNS: U5.6 (IO6); also elsewhere on the board
VBUS: C30.1, C31.1, D5.2 (A), Q4.3 (D), U7.5 (VBUS), U8.5 (VBUS)
VBUS_G: Q4.1 (G), Q5.3 (C), R27.1
VBUS_IN: J2.A4 (VBUS), J2.A9 (VBUS), J2.B4 (VBUS), J2.B9 (VBUS), PF2.1
VBUS_OV: Q5.1 (B), R28.2, U6.1 (K)
VBUS_OVS: R29.2, R30.1, U6.2 (REF)
VBUS_R: PF2.2, Q4.2 (S), Q5.2 (E), R28.1, R29.1

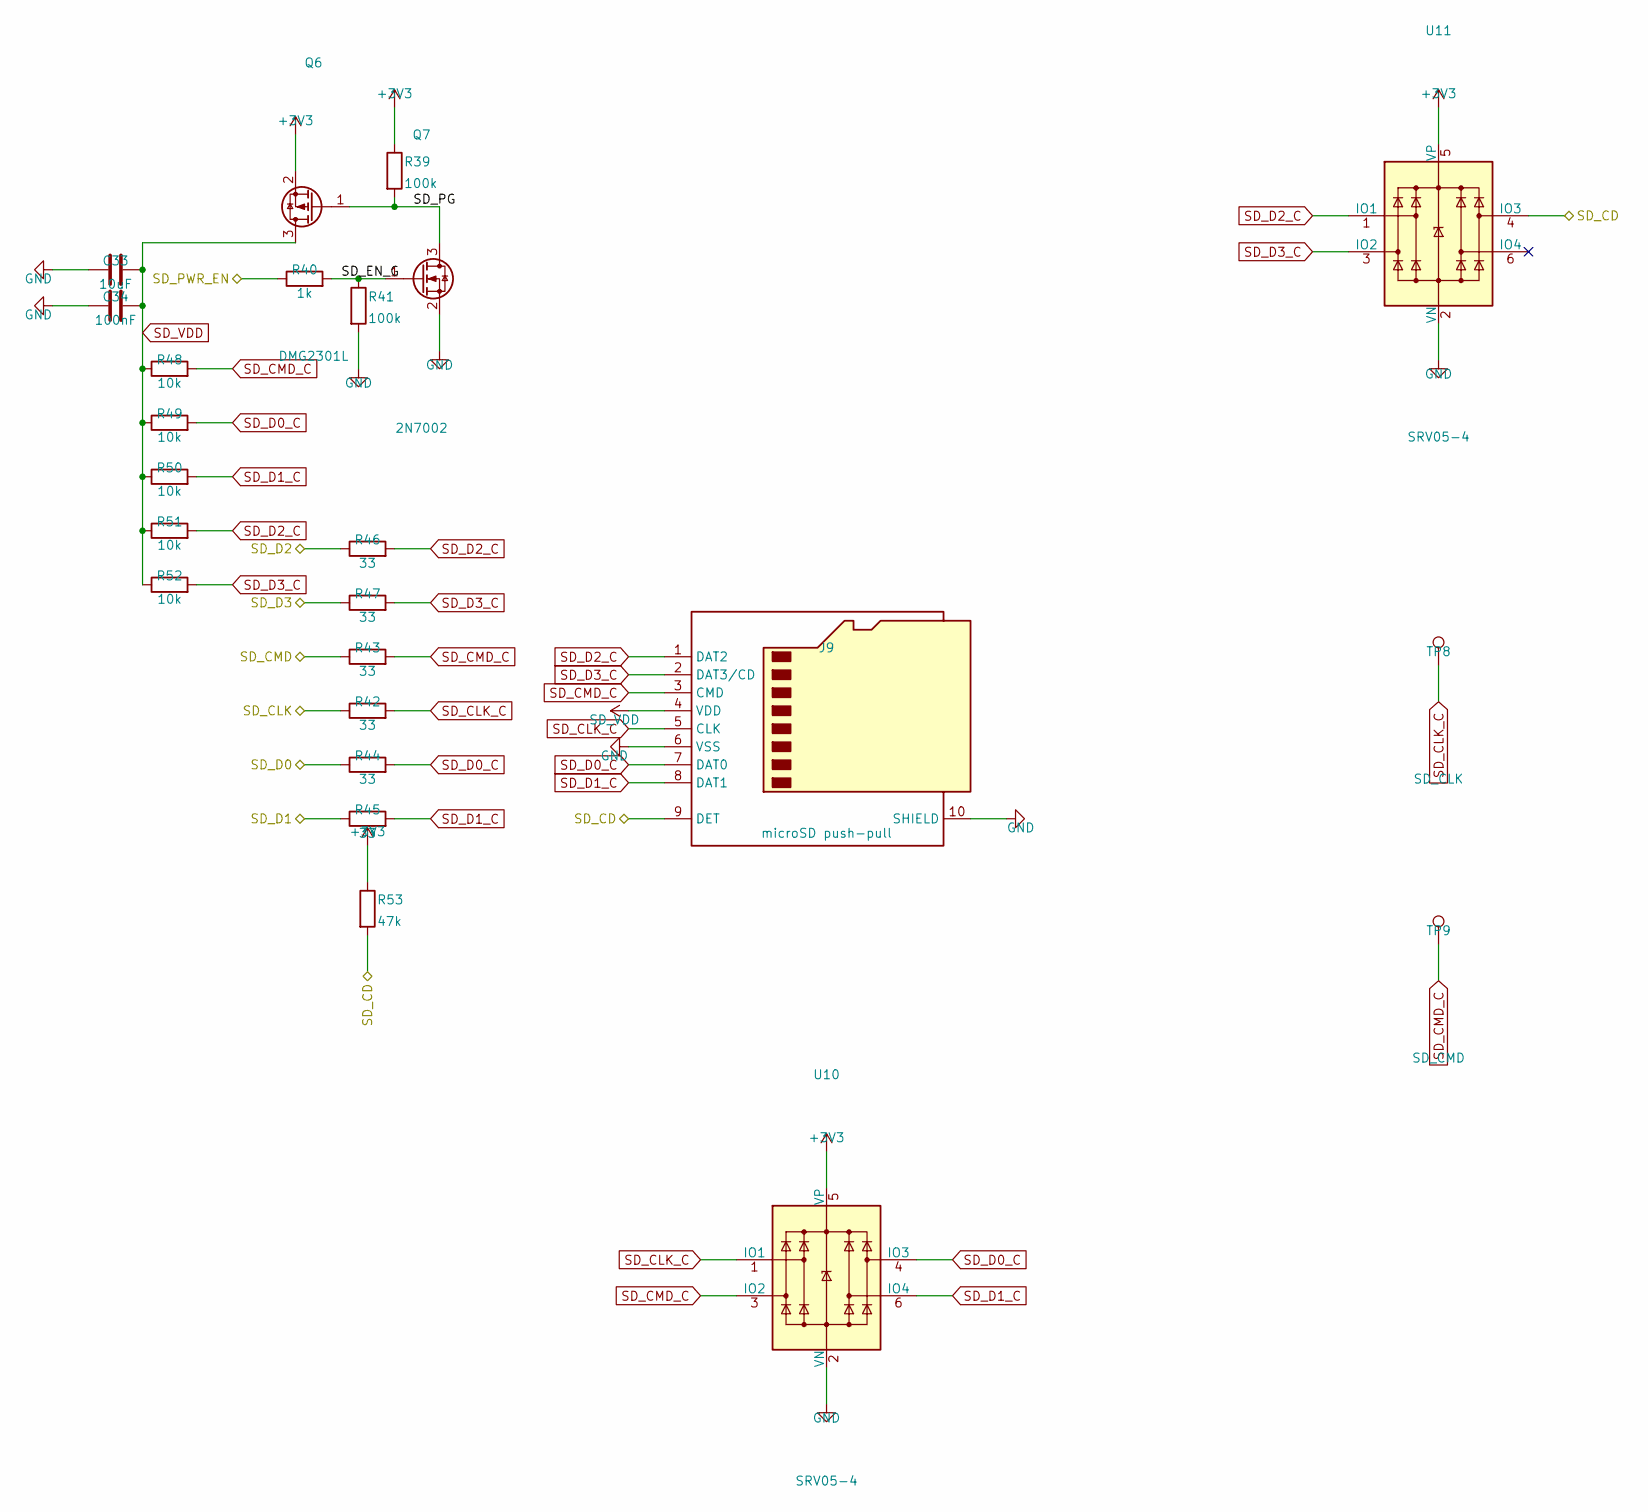
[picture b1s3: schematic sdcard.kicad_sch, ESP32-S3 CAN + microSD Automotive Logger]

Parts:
C33: 10uF; C_1206_3216Metric; Voltage 16V
C34: 100nF; C_0805_2012Metric; Voltage 16V
J9: microSD push-pull; microSD_HC_Hirose_DM3D-SF; MPN Hirose DM3D-SF
Q6: DMG2301L; SOT-23; MPN DMG2301L
Q7: 2N7002; SOT-23; MPN 2N7002
R39, R41: 100k; R_0805_2012Metric
R40: 1k; R_0805_2012Metric
R42, R43, R44, R45, R46, R47: 33; R_0805_2012Metric
R48, R49, R50, R51, R52: 10k; R_0805_2012Metric
R53: 47k; R_0805_2012Metric
TP8: SD_CLK; TestPoint_Pad_D1.5mm
TP9: SD_CMD; TestPoint_Pad_D1.5mm
U10, U11: SRV05-4; SOT-23-6; MPN Semtech SRV05-4.TCT

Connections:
+3V3: Q6.2 (S), R39.1, R53.1, U10.5 (VP), U11.5 (VP); also elsewhere on the board
SD_CD: J9.9 (DET), R53.2, U11.4 (IO3); also elsewhere on the board
SD_CLK: R42.1; also elsewhere on the board
SD_CLK_C: J9.5 (CLK), R42.2, TP8.1, U10.1 (IO1)
SD_CMD: R43.1; also elsewhere on the board
SD_CMD_C: J9.3 (CMD), R43.2, R48.2, TP9.1, U10.3 (IO2)
SD_D0: R44.1; also elsewhere on the board
SD_D0_C: J9.7 (DAT0), R44.2, R49.2, U10.4 (IO3)
SD_D1: R45.1; also elsewhere on the board
SD_D1_C: J9.8 (DAT1), R45.2, R50.2, U10.6 (IO4)
SD_D2: R46.1; also elsewhere on the board
SD_D2_C: J9.1 (DAT2), R46.2, R51.2, U11.1 (IO1)
SD_D3: R47.1; also elsewhere on the board
SD_D3_C: J9.2 (DAT3/CD), R47.2, R52.2, U11.3 (IO2)
SD_EN_G: Q7.1 (G), R40.2, R41.1
SD_PG: Q6.1 (G), Q7.3 (D), R39.2
SD_PWR_EN: R40.1; also elsewhere on the board
SD_VDD: C33.1, C34.1, J9.4 (VDD), Q6.3 (D), R48.1, R49.1, R50.1, R51.1, R52.1

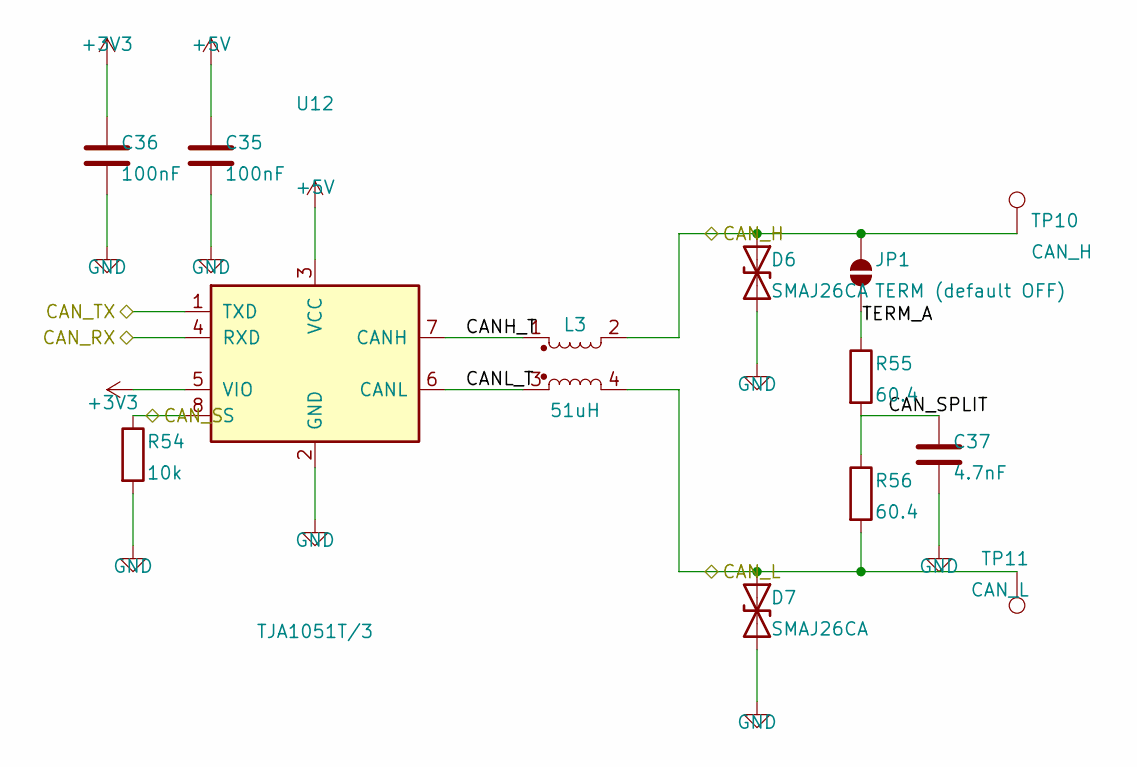
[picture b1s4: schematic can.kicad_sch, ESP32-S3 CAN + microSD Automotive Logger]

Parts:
C35, C36: 100nF; C_0805_2012Metric; Voltage 16V
C37: 4.7nF; C_0805_2012Metric; Voltage 50V
D6, D7: SMAJ26CA; D_SMA; MPN Diodes Inc SMAJ26CA-13-F
JP1: TERM (default OFF); SolderJumper-2_P1.3mm_Open_Pad1.0x1.5mm
L3: 51uH; L_CommonMode_TDK_ACT45B; MPN TDK ACT45B-510-2P-TL003
R54: 10k; R_0805_2012Metric
R55, R56: 60.4; R_0805_2012Metric
TP10: CAN_H; TestPoint_Pad_D1.5mm
TP11: CAN_L; TestPoint_Pad_D1.5mm
U12: TJA1051T/3; SOIC-8_3.9x4.9mm_P1.27mm; MPN TJA1051T/3,118

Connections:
+3V3: C36.1, U12.5 (VIO); also elsewhere on the board
+5V: C35.1, U12.3 (VCC); also elsewhere on the board
CANH_T: L3.1, U12.7 (CANH)
CANL_T: L3.3, U12.6 (CANL)
CAN_H: D6.1 (A1), JP1.1 (A), L3.2, TP10.1; also elsewhere on the board
CAN_L: D7.1 (A1), L3.4, R56.2, TP11.1; also elsewhere on the board
CAN_RX: U12.4 (RXD); also elsewhere on the board
CAN_S: R54.1, U12.8 (S); also elsewhere on the board
CAN_SPLIT: C37.1, R55.2, R56.1
CAN_TX: U12.1 (TXD); also elsewhere on the board
TERM_A: JP1.2 (B), R55.1
